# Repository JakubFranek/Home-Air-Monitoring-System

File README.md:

# Home Air Monitoring System

**Home Air Monitoring System (HAMS)** is my personal hardware & embedded software development project designed to monitor indoor and outdoor air quality in my home.

## Overview

The system consists of a [**central hub**](./docs/hub.md) and [**six wireless sensor nodes**](./docs/node.md) to measure:

- Temperature
- Relative Humidity
- Atmospheric Pressure
- Particulate Matter
- Volatile Organic Compounds (VOCs)
- NOₓ
- CO₂

## System Components

- **Central Hub**
   - **ESP32-based**; mains-powered.
   - Connects to the internet for weather updates and time synchronization via SNTP.
   - Displays real-time measurements on a 7.5" 800x480 e-ink screen with a 1 minute refresh rate.
   - Contains sensors for all previously listed quantities.
   - Screen-sized 3D-printed enclosure (estimated 175 mm x 92.65 mm x 120 mm).

- **Sensor Nodes**
   - **STM32-based** and battery-powered, optimized for low power consumption and long battery life.
   - Equipped with temperature and humidity sensors only, with optional hardware support for one more sensor.
   - Transmit data to the hub every minute using nRF24 radio modules.
   - Minimalistic and visually non-intrusive 3D-printed case with a small form factor (estimated 81 mm x 58 mm x 28 mm).

## Sensors

- **SHT40**
   - Temperature and humidity sensor from Sensirion.
   - Used in the central hub and sensor nodes.
   - Temperature accuracy: ±0.2 °C
   - Humidity accuracy: ±1.8 %RH
- **SCD41**
   - CO2 sensor from Sensirion.
   - Used in the central hub.
   - CO2 accuracy: ±50 ppm ± 5.0 %m.v. (depending on range)
- **SGP41**
   - VOC and NOx gas index sensor from Sensirion.
   - Used in the central hub.
- **SPS30**
   - Particulate matter sensor from Sensirion.
   - Used in the central hub.
   - Accuracy: ±10 %
- **BME280**
   - Temperature, relative humidity and atmospheric pressure sensor from Adafruit.
   - Used in the central hub (for atmospheric pressure only).
   - Atmospheric pressure accuracy: ±1 hPa

## Documentation

- [Hub](./docs/hub.md)
- [Nodes](./docs/node.md)
- [SHT4x calibration](./docs/sht4x_calibration.md)

## Repository Structure

```plaintext
├── docs                         # Documentation for project setup, usage, etc.
├── utilities                    # Various auxiliary scripts, tools etc.
│   ├── sht_sensor_burn_in       # PlatformIO Arduino project for SHT40 sensor burn-in
│   └── sht_sensor_calibration   # PlatformIO Arduino project for SHT40 sensor calibration
├── hub
│   ├── hardware                 # PCB design and schematic for hub
│   ├── firmware                 # Firmware for the ESP32-based central hub
│   └── 3D_models                # 3D models for the hub's enclosure
├── node
│   ├── firmware                 # Firmware for the STM32-based sensor nodes
│   ├── hardware                 # PCB designs and schematics for nodes
│   └── 3D_models                # 3D models for the nodes' enclosures
├── README.md                    # Project overview (you are reading this now!)
└── TODO.md                      # Project task list

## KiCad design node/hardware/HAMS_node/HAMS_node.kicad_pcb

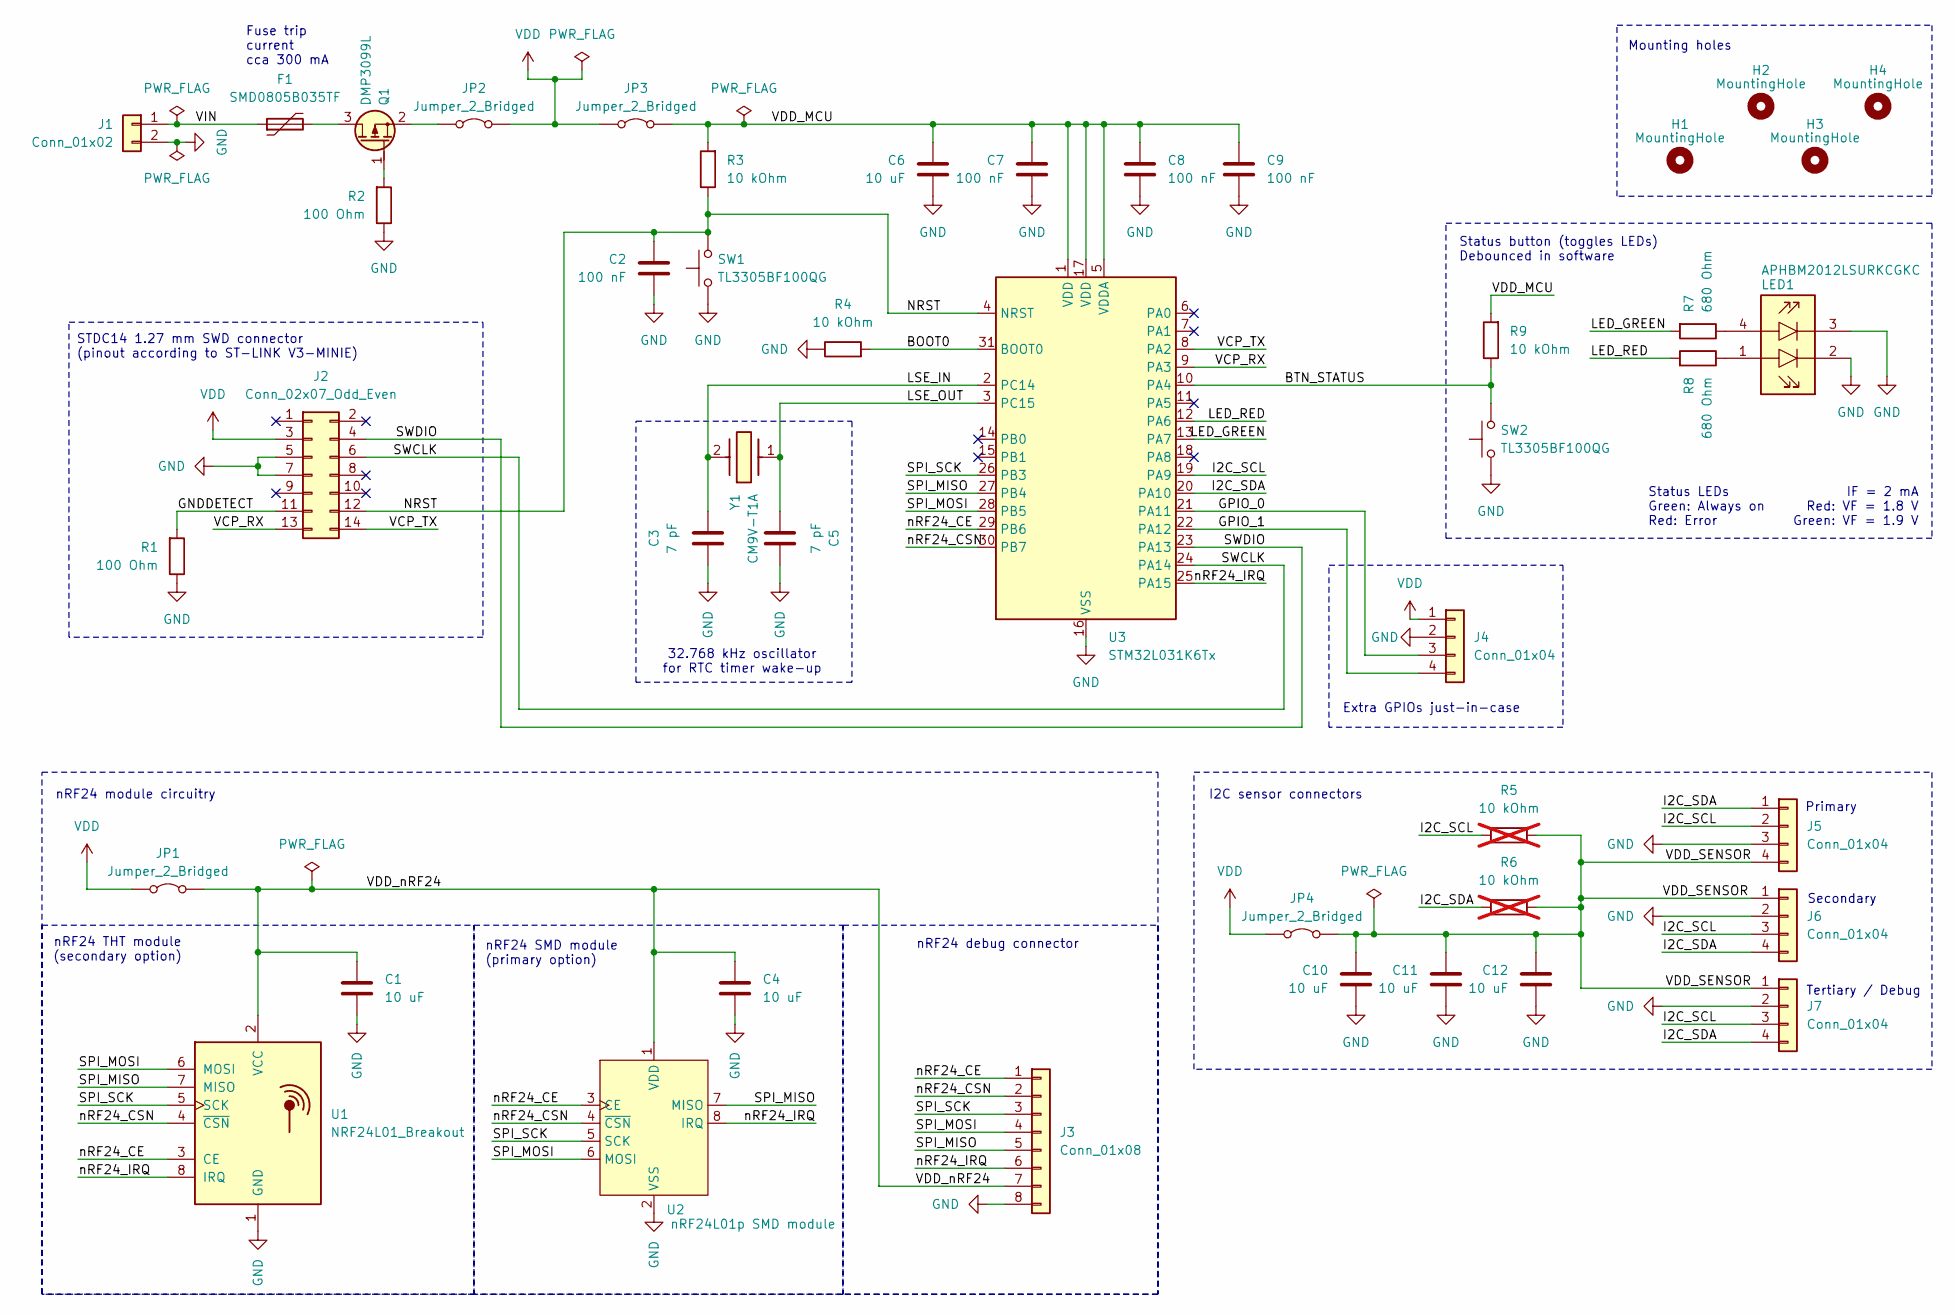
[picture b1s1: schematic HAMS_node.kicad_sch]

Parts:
C1, C4, C6, C10, C11, C12: 10 uF; C_0603_1608Metric_Pad1.08x0.95mm_HandSolder
C2, C7, C8, C9: 100 nF; C_0603_1608Metric_Pad1.08x0.95mm_HandSolder
C3, C5: 7 pF; C_0603_1608Metric_Pad1.08x0.95mm_HandSolder
F1: SMD0805B035TF; YAGEO_SMD0805_Fuse
H1, H2, H3, H4: MountingHole; MountingHole_2.2mm_M2_ISO7380
J1: Conn_01x02; JST_XH_B2B-XH-AM_1x02_P2.50mm_Vertical
J2: Conn_02x07_Odd_Even; PinHeader_2x07_P1.27mm_Vertical_SMD
J3: Conn_01x08; PinSocket_1x08_P2.54mm_Vertical
J4, J7: Conn_01x04; PinSocket_1x04_P2.54mm_Vertical
J5, J6: Conn_01x04; PinSocket_1x04_P2.54mm_Horizontal
JP1, JP2, JP3, JP4: Jumper_2_Bridged; PinHeader_1x02_P1.27mm_Vertical
LED1: APHBM2012LSURKCGKC; KPHBM2012QBDCGKC; Mouser Part Number 604-APHBM2012LSURKCG
Q1: DMP3099L; SOT-23
R1, R2: 100 Ohm; R_0603_1608Metric_Pad0.98x0.95mm_HandSolder
R3, R4, R9: 10 kOhm; R_0603_1608Metric_Pad0.98x0.95mm_HandSolder
R5, R6: 10 kOhm; R_0603_1608Metric_Pad0.98x0.95mm_HandSolder; not fitted
R7, R8: 680 Ohm; R_0603_1608Metric_Pad0.98x0.95mm_HandSolder
SW1, SW2: TL3305BF100QG; E-Switch_TL3305BF100QG_Tactile_SPST
U1: NRF24L01_Breakout; nRF24L01_Breakout
U2: nRF24L01p SMD module; nRF24L01p_SMD_module
U3: STM32L031K6Tx; LQFP-32_7x7mm_P0.8mm
Y1: CM9V-T1A; Crystal_SMD_MicroCrystal_CM9V-T1A-2Pin_1.6x1.0mm_BigPads; Mouser Part Number 428-202416-MC01

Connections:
/BOOT0: R4.2, U3.31 (BOOT0)
/BTN_STATUS: R9.1, SW2.2, U3.10 (PA4)
/GNDDETECT: J2.11, R1.2
/GPIO_0: J4.3, U3.21 (PA11)
/GPIO_1: J4.4, U3.22 (PA12)
/I2C_SCL: J5.2, J6.3, J7.3, R5.1, U3.19 (PA9)
/I2C_SDA: J5.1, J6.4, J7.4, R6.1, U3.20 (PA10)
/LED_GREEN: R7.2, U3.13 (PA7)
/LED_RED: R8.2, U3.12 (PA6)
/LSE_IN: C3.1, U3.2 (PC14), Y1.2 (X2)
/LSE_OUT: C5.1, U3.3 (PC15), Y1.1 (X1)
/NRST: C2.1, J2.12, R3.1, SW1.2, U3.4 (NRST)
/SPI_MISO: J3.5, U1.7 (MISO), U2.7 (MISO), U3.27 (PB4)
/SPI_MOSI: J3.4, U1.6 (MOSI), U2.6 (MOSI), U3.28 (PB5)
/SPI_SCK: J3.3, U1.5 (SCK), U2.5 (SCK), U3.26 (PB3)
/SWCLK: J2.6, U3.24 (PA14)
/SWDIO: J2.4, U3.23 (PA13)
/VCP_RX: J2.13, U3.9 (PA3)
/VCP_TX: J2.14, U3.8 (PA2)
/VDD_MCU: C6.1, C7.1, C8.1, C9.1, JP3.2 (B), R3.2, R9.2, U3.1 (VDD), U3.5 (VDDA), U3.17 (VDD)
/VDD_SENSOR: C10.1, C11.1, C12.1, J5.4, J6.1, J7.1, JP4.2 (B), R5.2, R6.2
/VDD_nRF24: C1.2, C4.2, J3.7, JP1.2 (B), U1.2 (VCC), U2.1 (VDD)
/VIN: F1.1, J1.1
/nRF24_CE: J3.1, U1.3 (CE), U2.3 (CE), U3.29 (PB6)
/nRF24_CSN: J3.2, U1.4 (~CSN), U2.4 (~CSN), U3.30 (PB7)
/nRF24_IRQ: J3.6, U1.8 (IRQ), U2.8 (IRQ), U3.25 (PA15)
GND: C1.1, C2.2, C3.2, C4.1, C5.2, C6.2, C7.2, C8.2, C9.2, C10.2, C11.2, C12.2, J1.2, J2.5, J2.7, J3.8, J4.2, J5.3, J6.2, J7.2, LED1.2 (CATHODE_RED), LED1.3 (CATHODE_GREEN), R1.1, R2.1, R4.1, SW1.1, SW2.1, U1.1 (GND), U2.2 (VSS), U3.16 (VSS), U3.32 (VSS)
unnamed: JP2.1 (A), Q1.2 (S)
unnamed: LED1.4 (ANODE_GREEN), R7.1
unnamed: LED1.1 (ANODE_RED), R8.1
unnamed: F1.2, Q1.3 (D)
unnamed: Q1.1 (G), R2.2
VDD: J2.3, J4.1, JP1.1 (A), JP2.2 (B), JP3.1 (A), JP4.1 (A)

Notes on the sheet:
nRF24 THT module (secondary option)
IF = 2 mA Red: VF = 1.8 V Green: VF = 1.9 V
nRF24 SMD module (primary option)
32.768 kHz oscillator for RTC timer wake-up
Mounting holes
Fuse trip current cca 300 mA
Status LEDs Green: Always on Red: Error
Secondary
nRF24 debug connector
Tertiary / Debug
Status button (toggles LEDs) Debounced in software
STDC14 1.27 mm SWD connector (pinout according to ST-LINK V3-MINIE)
Primary
Extra GPIOs just-in-case
I2C sensor connectors
nRF24 module circuitry

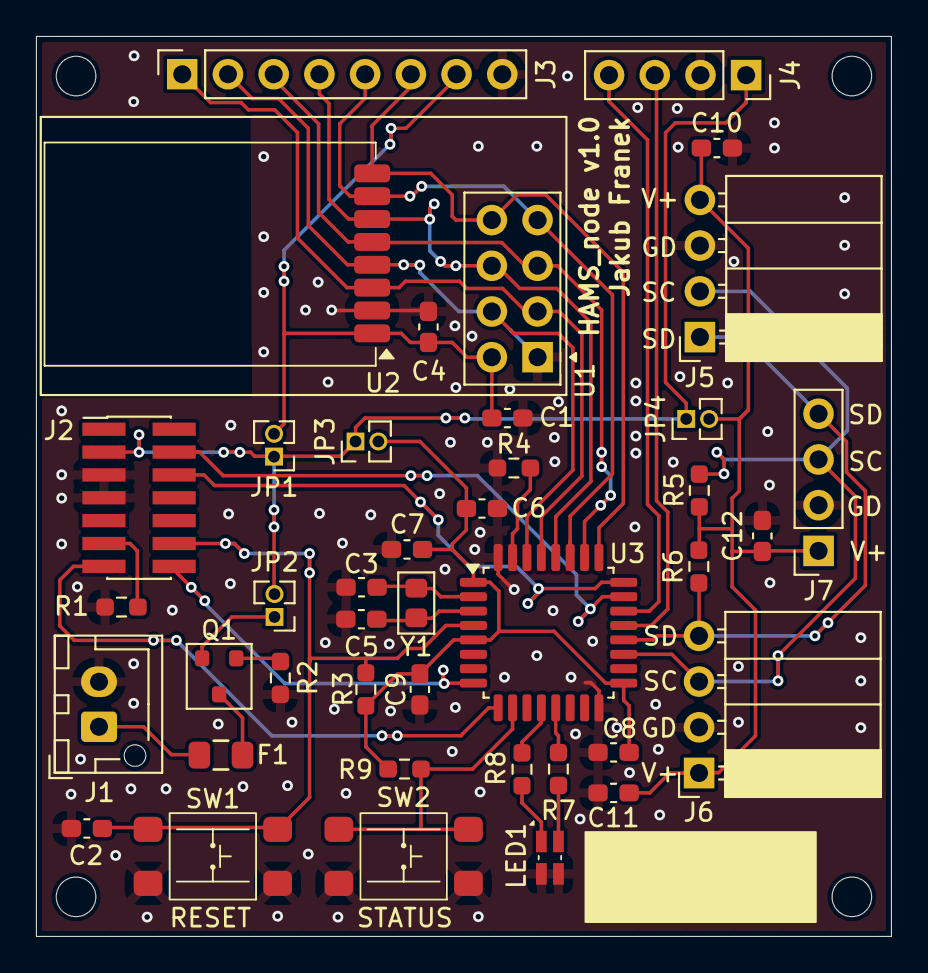
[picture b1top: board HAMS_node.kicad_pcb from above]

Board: 2 copper layers, 47.5 x 50.0 mm, 45 parts (0 on the bottom side), 33 nets.

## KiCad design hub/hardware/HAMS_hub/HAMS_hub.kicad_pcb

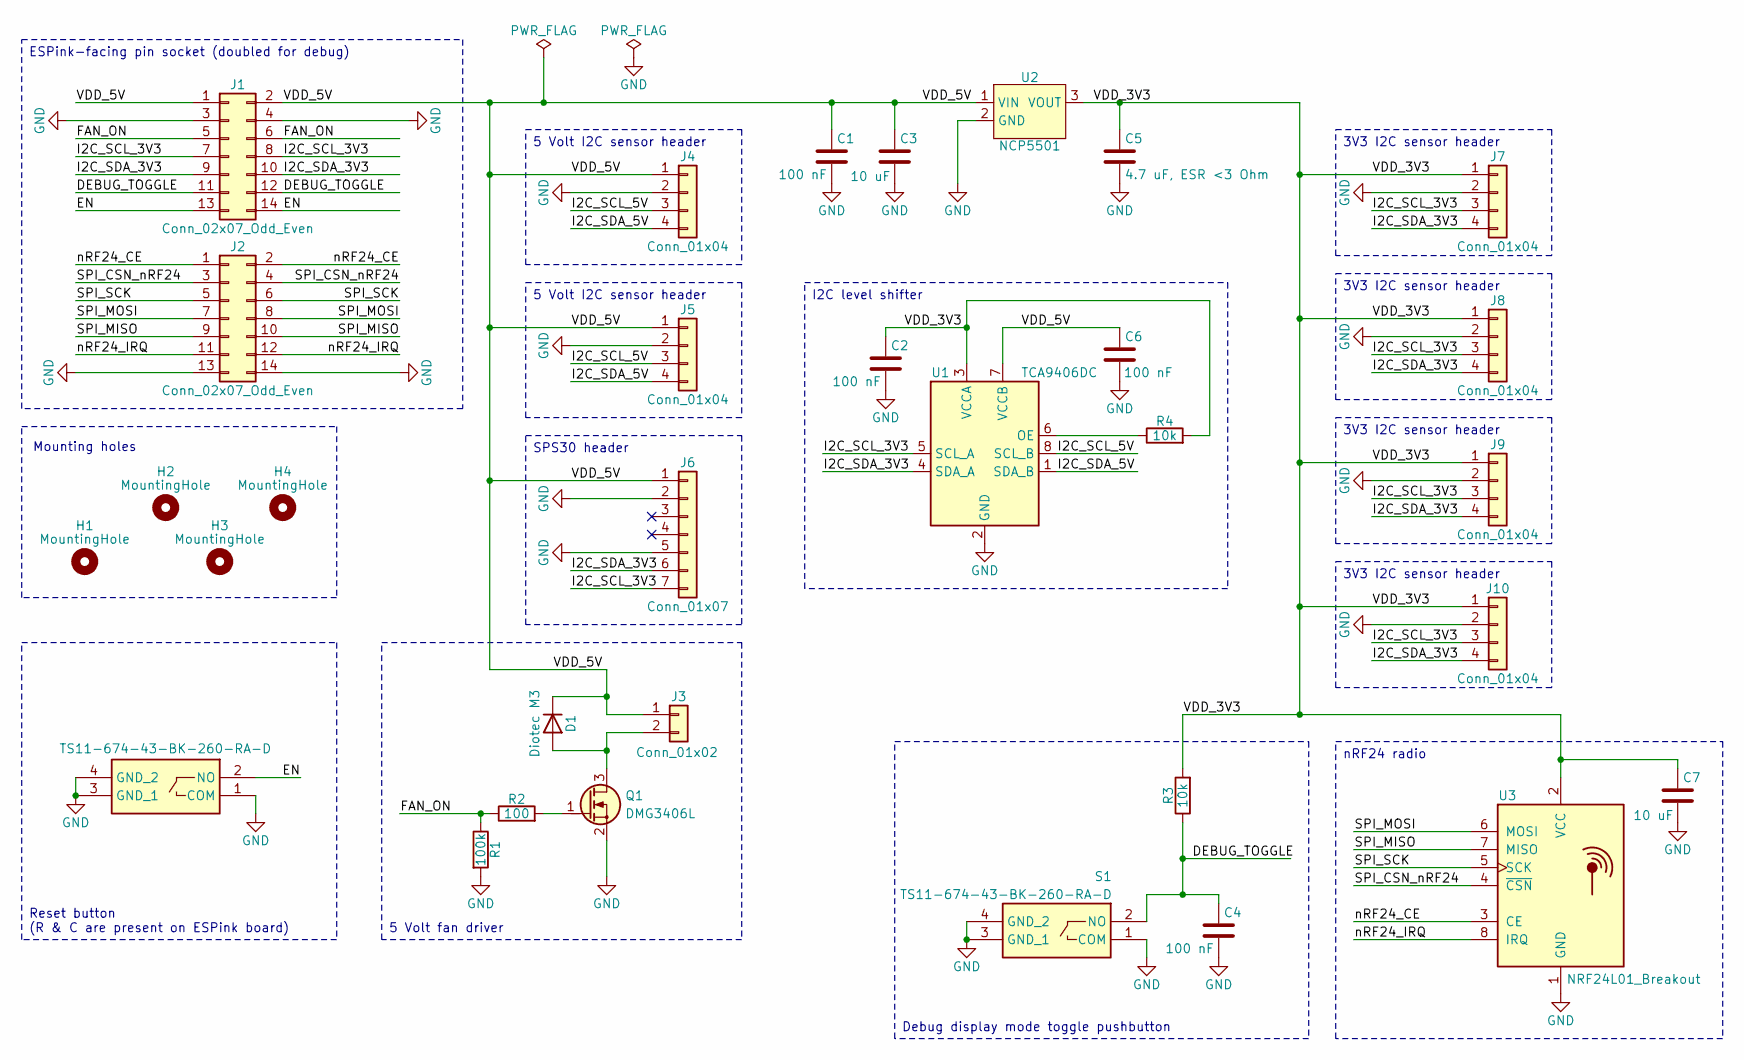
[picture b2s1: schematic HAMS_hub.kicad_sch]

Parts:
C1, C2, C4, C6: 100 nF; C_0805_2012Metric_Pad1.18x1.45mm_HandSolder
C3, C7: 10 uF; C_0805_2012Metric_Pad1.18x1.45mm_HandSolder
C5: 4.7 uF, ESR <3 Ohm; C_0805_2012Metric_Pad1.18x1.45mm_HandSolder
D1: Diotec M3; D_SMA_Handsoldering
H1, H2, H3, H4: MountingHole; MountingHole_2.2mm_M2_ISO7380
J1, J2: Conn_02x07_Odd_Even; PinSocket_2x07_P2.54mm_Vertical
J3: Conn_01x02; PinHeader_1x02_P2.54mm_Vertical
J4, J5, J7, J8, J9, J10: Conn_01x04; PinSocket_1x04_P2.54mm_Vertical
J6: Conn_01x07; PinHeader_1x07_P2.54mm_Vertical
Q1: DMG3406L; SOT-23
R1: 100k; R_0805_2012Metric_Pad1.20x1.40mm_HandSolder
R2: 100; R_0805_2012Metric_Pad1.20x1.40mm_HandSolder
R3, R4: 10k; R_0805_2012Metric_Pad1.20x1.40mm_HandSolder
S1, S2: TS11-674-43-BK-260-RA-D; TS1167443BK260RAD; Mouser Part Number 179-TS1167443260RAD
U1: TCA9406DC; SSOP-8_2.95x2.8mm_P0.65mm
U2: NCP5501; TO-252-2
U3: NRF24L01_Breakout; nRF24L01_Breakout

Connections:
/DEBUG_TOGGLE: C4.1, J1.11, J1.12, R3.1, S1.2 (NO)
/EN: J1.13, J1.14, S2.2 (NO)
/FAN_ON: J1.5, J1.6, R1.1, R2.1
/I2C_SCL_3V3: J1.7, J1.8, J6.7, J7.3, J8.3, J9.3, J10.3, U1.5 (SCL_A)
/I2C_SCL_5V: J4.3, J5.3, U1.8 (SCL_B)
/I2C_SDA_3V3: J1.9, J1.10, J6.6, J7.4, J8.4, J9.4, J10.4, U1.4 (SDA_A)
/I2C_SDA_5V: J4.4, J5.4, U1.1 (SDA_B)
/SPI_CSN_nRF24: J2.3, J2.4, U3.4 (~CSN)
/SPI_MISO: J2.9, J2.10, U3.7 (MISO)
/SPI_MOSI: J2.7, J2.8, U3.6 (MOSI)
/SPI_SCK: J2.5, J2.6, U3.5 (SCK)
/VDD_3V3: C2.1, C5.1, C7.1, J7.1, J8.1, J9.1, J10.1, R3.2, R4.2, U1.3 (VCCA), U2.3 (VOUT), U3.2 (VCC)
/VDD_5V: C1.1, C3.1, C6.1, D1.1 (K), J1.1, J1.2, J3.1, J4.1, J5.1, J6.1, U1.7 (VCCB), U2.1 (VIN)
/nRF24_CE: J2.1, J2.2, U3.3 (CE)
/nRF24_IRQ: J2.11, J2.12, U3.8 (IRQ)
GND: C1.2, C2.2, C3.2, C4.2, C5.2, C6.2, C7.2, J1.3, J1.4, J2.13, J2.14, J4.2, J5.2, J6.2, J6.5, J7.2, J8.2, J9.2, J10.2, Q1.2 (S), R1.2, S1.1 (COM), S1.3 (GND_1), S1.4 (GND_2), S2.1 (COM), S2.3 (GND_1), S2.4 (GND_2), U1.2 (GND), U2.2 (GND), U3.1 (GND)
unnamed: D1.2 (A), J3.2, Q1.3 (D)
unnamed: Q1.1 (G), R2.2
unnamed: R4.1, U1.6 (OE)

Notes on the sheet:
Mounting holes
Debug display mode toggle pushbutton
3V3 I2C sensor header
5 Volt I2C sensor header
5 Volt fan driver
ESPink-facing pin socket (doubled for debug)
nRF24 radio
I2C level shifter
SPS30 header
Reset button (R & C are present on ESPink board)

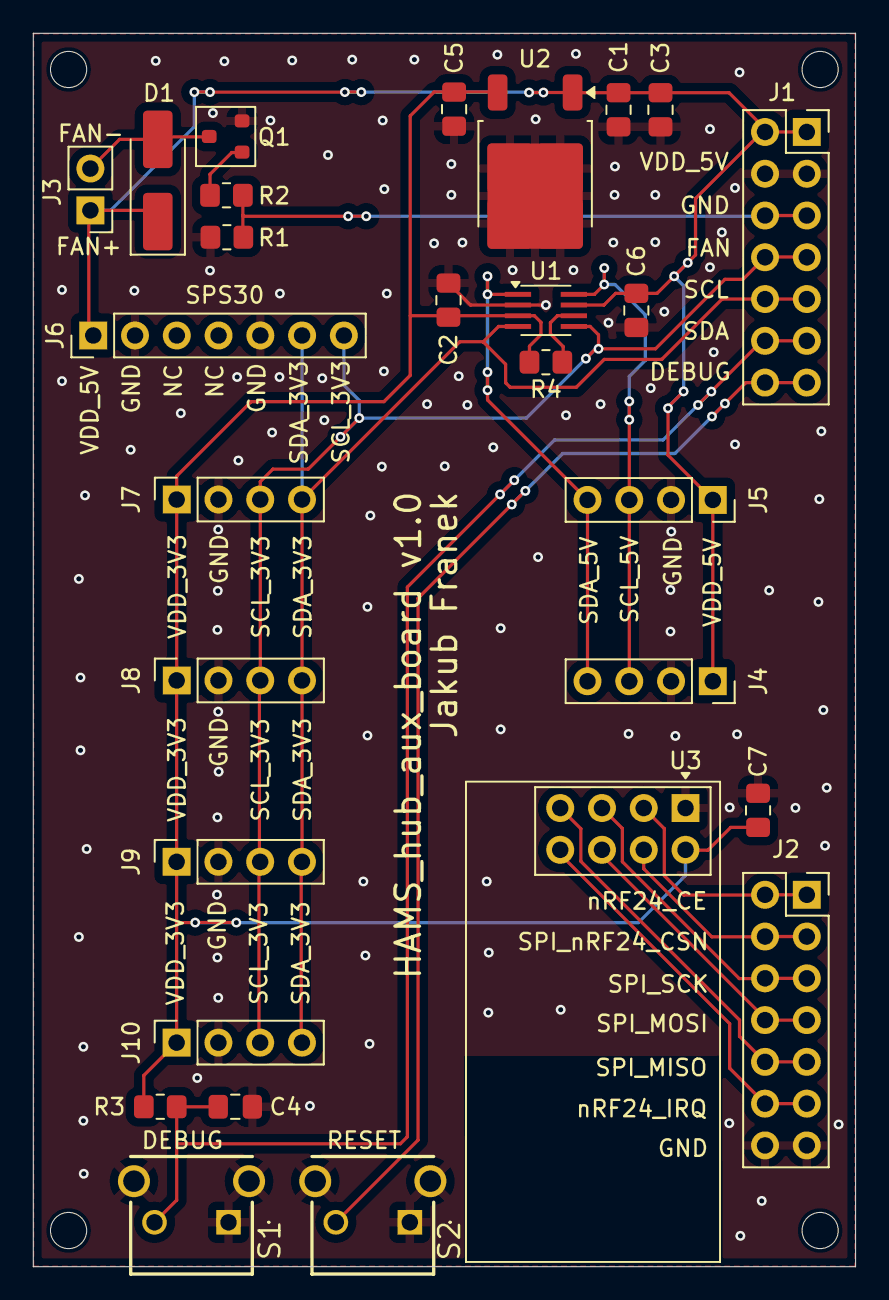
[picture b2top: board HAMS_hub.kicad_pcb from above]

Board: 2 copper layers, 50.0 x 75.0 mm, 32 parts (0 on the bottom side), 19 nets.

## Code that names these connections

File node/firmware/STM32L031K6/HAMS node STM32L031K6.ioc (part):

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Mcu.Name=STM32L031K(4-6)Tx
Mcu.Package=LQFP32
Mcu.UserName=STM32L031K6Tx
PA10.GPIOParameters=GPIO_Speed,GPIO_Label
PA10.GPIO_Label=I2C_SDA
PA10.GPIO_Speed=GPIO_SPEED_FREQ_LOW
PA10.Mode=I2C
PA10.Signal=I2C1_SDA
PA13.Mode=Serial_Wire
PA13.Signal=SYS_SWDIO
PA14.Mode=Serial_Wire
PA14.Signal=SYS_SWCLK
PA15.GPIOParameters=GPIO_Label,GPIO_ModeDefaultEXTI
PA15.GPIO_Label=nRF24_IRQ
PA15.GPIO_ModeDefaultEXTI=GPIO_MODE_IT_FALLING
PA15.Signal=GPXTI15
PA2.Mode=Asynchronous
PA2.Signal=USART2_TX
PA3.Mode=Asynchronous
PA3.Signal=USART2_RX
PA4.GPIOParameters=GPIO_Label,GPIO_ModeDefaultEXTI
PA4.GPIO_Label=BUTTON_LED
PA4.GPIO_ModeDefaultEXTI=GPIO_MODE_IT_FALLING
PA4.Signal=GPXTI4
PA6.GPIOParameters=GPIO_Label
PA6.GPIO_Label=LED_ERROR
PA6.Signal=GPIO_Output
PA7.GPIOParameters=GPIO_Label
PA7.GPIO_Label=LED_STATUS
PA7.Signal=GPIO_Output
PA9.GPIOParameters=GPIO_Speed,GPIO_Label
PA9.GPIO_Label=I2C_SCL
PA9.GPIO_Speed=GPIO_SPEED_FREQ_LOW
PA9.Mode=I2C
PA9.Signal=I2C1_SCL
PB3.GPIOParameters=GPIO_Label
PB3.GPIO_Label=SPI_SCK
PB3.Mode=Full_Duplex_Master
PB3.Signal=SPI1_SCK
PB4.GPIOParameters=GPIO_Label
PB4.GPIO_Label=SPI_MISO
PB4.Mode=Full_Duplex_Master
PB4.Signal=SPI1_MISO
PB5.GPIOParameters=GPIO_Label
PB5.GPIO_Label=SPI_MOSI
PB5.Mode=Full_Duplex_Master
PB5.Signal=SPI1_MOSI
PB6.GPIOParameters=GPIO_Label
PB6.GPIO_Label=nRF24_CE
PB6.Signal=GPIO_Output
PB7.GPIOParameters=GPIO_Label
PB7.GPIO_Label=nRF24_CSN
PB7.Signal=GPIO_Output
PC14-OSC32_IN.GPIOParameters=GPIO_Label
PC14-OSC32_IN.GPIO_Label=LSE_IN
PC14-OSC32_IN.Mode=LSE-External-Oscillator
PC14-OSC32_IN.Signal=RCC_OSC32_IN
PC15-OSC32_OUT.GPIOParameters=GPIO_Label
PC15-OSC32_OUT.GPIO_Label=LSE_OUT
PC15-OSC32_OUT.Mode=LSE-External-Oscillator
PC15-OSC32_OUT.Signal=RCC_OSC32_OUT
RCC.HSE_VALUE=8000000
RCC.SYSCLKFreq_VALUE=8000000
RCC.SYSCLKSource=RCC_SYSCLKSOURCE_PLLCLK
board=custom

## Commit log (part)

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2024-11-07 Initial commit
    Transmitter code in incomplete state.
    Initial README.md implementation.
2024-11-07 Improve HAMS node FW: stop mode, bug fixes
    Improve stop mode current consumption (<1 uA reached).
    Add several pin user labels.
    Set unused pins to analog mode.
    Fix bug: incorrect I2C/SPI timeout logic.
    Fix bug: event flags cleared incorrectly in app.c.
2024-11-08 Improve HAMS node FW: refactoring, bug fixes
    Add macros to make app.c code less repetitive.
    Disable LED pin (not used in final application).
    Fix bug: large stop mode current consumption (pins not set to analog
    mode).
2024-11-09 Improve HAMS node FW: f_CLK, sleep, SPI
    Lower clock from 32 MHz to 8 MHz.
    Increase I2C and SPI frequency 4x.
    Enter sleep mode when waiting for timer and nRF24 interrupts.
    Force nRF24_CE pin low during stop mode.
    Add SPI1_Transmit_Multi function optimized for transmitting multiple
    bytes in quick succession.
2024-11-09 Improve HAMS node FW: optimize SPI, refactor
    Optimize SPI custom functions for speed.
    Make all SPI and I2C custom functions handle multi-byte transfers.
    Add const modifiers to relevant function signatures.
    Remove redundant status code returns from many functions.
2024-11-09 Improve HAMS node FW: ADC, app errors, refactoring
    Measure VDDA via ADC and send it via nRF24 in payload.
    Add more AppError enum members, modify error checking macros in app.c to
    use them.
2024-12-02 Improve HAMS node FW: fix bug, format, add TODO
2024-12-02 Update task list
2024-12-17 Update task list, add resource images
2024-12-18 Add initial HAMS hub FW
    Initial commit of HAMS hub firmware (copied from EPD demo project).
    Update .gitignore.
2024-12-18 Improve HAMS hub FW
    Move display functions to a separate file.
    Add custom memory partition table (code would not fit in default
    1 MB partition).
    Implement WiFi station module.
    Implement SNTP module.
    Implement svatkyAPI.cz module.
2024-12-19 Improve HAMS hub FW: SHT4x & SGP41 sensors
    Add sensor_control module with support for SHT4x and SGP41 sensors.
    Add timeout to openweathermap_api request_weather_data function.
    Add timeout to svatky_api request_svatky_data function.
    Rename wifi_sta to wifi_station.
2024-12-19 Improve HAMS hub FW: BME280 sensor
    Add support for BME280 sensor.
2024-12-19 Improve HAMS hub FW: SCD41 sensor
    Add support for SCD41 sensor.
    Add Sgp41Device.sampling_period_s member.
2024-12-19 Improve HAMS hub FW: SPS30 sensor
    Add support for SPS30 sensor.
    Add delay function pointer to SGP41 driver to fix I2C errors.
    Merge sgp41_execute_self_test and sgp41_evaluate_self_test into one
    function.
2024-12-19 Improve HAMS hub FW: SPS30 sensor
    Increase I2C function timeout periods to 20 ms.
    Add code to main.cpp to print formatted timezone-aware time.
2024-12-19 Improve HAMS node FW: fix bug, lengthen sleep
    Lengthen sleep to 10 seconds.
    Fix bug: received data is 3 transmissions delayed (flush nRF24 TX FIFO
    before transmitting).
2024-12-19 Improve HAMS hub FW: refactor
    Add how-to guides to BME280 and nRF24 drivers.
    Move private nRF24 driver defines from .h to .c file.
2024-12-20 Improve HAMS node FW: refactor, fix bug
    Rename app_error variable to app_status.
    Add another TX FIFO flush command to prevent delayed data transmissions.
    Update task list.
2024-12-20 Improve HAMS hub FW: add timestamps
    Add timestamps to SvatkyApiData and WeatherData.
2024-12-20 Improve HAMS hub FW: refactor radio control
    Add nodes.h with node name and address definitions.
    Add timestamp to NodeData.
    Move NodeDataSet mutex to static radio_control.c variable.
2024-12-20 Improve HAMS hub FW: refactor radio control
    Remove NodeDataSet struct (it was only encapsulating a single array).
2024-12-20 Improve HAMS hub FW: fix bug, display real data
    Fix bug: radio_control function get_node_data does not copy data
    properly.
    Store hub's sensor data in SensorHubData struct.
    Show real data on e-ink display.
2024-12-20 Improve HAMS hub FW: startup sequence logging
    Add startup sequence logging to e-ink display to main.cpp.
    Update task list.
    Change FreeSans10pt7b yAdvance from 33 to 22 px.
    Add wifi_station docstrings, function status codes and function
    is_wifi_connected.
    Add sntp_api docstrings and function status codes.
2024-12-20 Improve HAMS hub FW: add debug mode
    Add button driven debug mode.
    Change get_wifi_ap_record to provide more information to DisplayData
    struct directly.
    Add svatkyapi and openweathermap update counts their data structs.
    Add SNTP debug info to DisplayData, and support it in sntp_api.
    Add measurement counts to SensorHubData struct.
2024-12-20 Improve HAMS hub FW: minor improvements
    Update task list.
    Use current date in svatkyapi request.
    Request new weather forecast as soon as the date changes.
    Add display_control function docstrings.
    Fix bug: replace Czech characters in the nameday name.
2024-12-21 Improve HAMS hub FW: minor improvements
    Add 8 pt font for debug mode.
    Improve debug mode layout and add app status code.
    Save sensor status codes to SensorHubData.
    Add synchronize_time function to sntp_api.
    Refactor sntp_api.
    Add connect_wifi method to wifi_station.
2024-12-21 Improve HAMS node FW: minor refactor
    Move flush command from phase 1 to phase 2 state.
    Fix flush command position in awaiting ack state
2024-12-21 Improve HAMS hub FW: improve debug mode
    Implement hub sensor error count debug mode values.
    Implement WiFi connection count debug mode value.
2024-12-21 Improve HAMS hub FW: handle invalid display data
    Display "--" when data is out of date or invalid.
2024-12-23 Improve HAMS hub FW: refactor, fix bugs
    Update task list.
    Add calendar_data, hams_data and weather_data headers which
    include common struct definitions.
    Create DebugData struct, which is now a member of HamsData
    (previously DisplayData).
    Fix bug: rain and snow WeatherData members not reset to zero when their
2024-12-27 Improve HAMS hub FW: refactor
    Add & improve comments/docstrings in multiple files.
    Rename nodes.h/c to node_constants.h/c.
    Rename sntp_api to sntp_control.
    Add get_sntp_stats function to sntp_api.
    Rename wifi_station to wifi_station_control.
    Add logging, connection counting, error checking to
2024-12-27 Improve HAMS hub FW: fix bug, utilize second CPU
    Fix bug: typical particulate matter particle size unit is nm, but
    should be um.
    Run task_nrf24_control on second core (PRO_CPU).
2024-12-28 Add calibration PlatformIO utility project
    Add utilities/temp_relhum_sensor_calibration PlatformIO project.
2024-12-28 Improve project docs and structure
    Update task list.
    Update README.
    Rename temp_relhum_sensor_calibration project to sht_sensor_calibration.
    Add tiny hub FW improvements.
2024-12-29 Add SHT40 burn-in PlatformIO utility project
    Update task list.
2024-12-30 Improve SHT40 calibration utility project
    Toggle MOSFET to draw more current periodically in order to prevent
    power bank from switching off.
2024-12-30 Improve HAMS node HW: add WIP PCB, edit schematic
    Update schematic significantly (adding nRF24 modules, specify parts, add
    notes etc).
    Add preliminary PCB layout (WIP).
2024-12-30 Improve HAMS node HW: PCB and device resize
    Change many 0805 devices for 0603 devices.
    Add mounting holes.
    Make the board 4.5 x 5 cm size.
2025-01-04 Improve HAMS node HW: PCB resize, optimization
    Optimize MCU pinout with respect to PCB routing.
    Change PCB size to 47.5 mm x 50 mm.
2025-01-05 Update task list
    Remove redundant .gitignore files.
2025-01-08 Improve HAMS node HW: schematic and PCB
    Add UART support to the ST-LINK programmer header.
    Update task list.
2025-01-15 Improve HAMS node HW: PCB
    Update HAMS_node PCB layout (minor position changes).
    Update task list.
2025-01-15 Improve HAMS hub FW: fix bug
    Fix bug: error codes printed in debug messages are unrelated to the
    given sensors.
2025-01-15 Add HAMS hub HW KiCad files (WIP)
    HAMS hub schematic is work-in-progress.
2025-01-17 Improve HAMS hub HW: schematic and PCB
    Improve schematic (add debug headers and mounting holes).
    Add DRC-clean PCB design.
    Update task list.
2025-01-26 Improve HAMS node FW: button driven status LEDs
    Add code for handling a button which causes status LEDs to light up.
2025-01-26 Improve HAMS node FW: remap pins
2025-01-27 Improve HAMS hub HW: reset button
    Add reset button.
2025-01-27 Improve HAMS hub HW: status button rework
    Replace toggle switch with tactile switch for status button.
2025-01-27 Update task list
    Check in .ioc HAMS node FW file.
2025-01-30 Add HAMS node & hub PCB gerbers
2025-02-08 Add HAMS node & hub 3D models, update task list
    Update task list.
    Update .gitignore.
    Add HAMS hub and node PCB 3D models.
    Add HAMS hub case 3D model.
2025-02-12 Update README and task list
2025-02-26 Update KiCAD files to version 9
2025-02-26 Add interactive BOMs
2025-02-26 Improve HAMS node FW: update nRF24 driver (bugged)
    Update task list.
2025-02-26 Improve HAMS node FW: fix nRF24 bug
    Fix bugged nRF24 by adding missing IRQ mask values when initializing
    nRF24 struct.
    Make leds_on and button_pending variables boolean.
2025-02-27 Improve HAMS node FW: auto retransmit delay
    Make nRF24 auto retransmit delay tied to node ID, so that it is
    unique for each node.
2025-03-01 Improve HAMS node FW: fix bugs, refactor UART logs
    Update task list.
    Fix bug: incorrect auto retransmit delay calculation.
    Refactor UART debug logging and debug mode (previously leds_on).
2025-03-01 Improve HAMS node HW & FW
    Add HAMS node small case 3D printing files.
    Update SHT4x driver in HAMS node firmware.
    Add comments and docstrings to HAMS node firmware.
    Update task list.
2025-03-01 Add firmware documentation
    Update task list.
2025-03-02 Add SHT4x calibration documentation
2025-03-05 Update 3D printing files
2025-03-09 Add hardware photos, update task list
2025-03-16 Improve HAMS node FW: fix bug, set period to 60 s
    Fix bug: nRF24 clones require CE pulse much longer than 10 us to
    transmit.
    Increase wake up period to 60 seconds.
2025-03-16 Update documentation
2025-03-16 Update hub FW
    Update task list.
    Rotate display to match enclosure orientation.
    Make 24h temperature minimum display optional and disable it.
    Add SCD41 FRC correction factor value to debug mode display.
    Simplify node info in debug display.
    Add code to allow SPS30 measurements at different rates (currently still
2025-03-16 Improve HAMS node & hub FW, fix bugs
    Set node and hub nRF24 data rate to 250 kbps.
    Fix bug: incorrect register bit field position values in nRF24 driver
    header.
    Fix bug: incorrect atmospheric pressure units.
    Rename node "Detsky pok." to "Detsky pokoj".
    Shorten node debug mode text.
2025-03-16 Update task list and README
2025-03-16 Fix node documentation
2025-03-17 Add 3D printing files, update task list
2025-03-17 Remove redundant 3D printing files
2025-03-17 Add image, improve README
2025-03-17 Remove redundant 3D printing file
2025-03-17 Improve documentation
    Fix image link in Markdown.
2025-05-08 Add issues doc
2025-05-08 Improve HAMS node FW: bug fix, slow down TIM21
    Slow down TIM21 by a factor of 10 (from 1 us to 10 us period),
    to allow scheduling interrupts for later.
    Fix bug: app_status not assigned in handle_state_awaiting_ack function
    when nRF24 IRQ times out.
    Fix bug: nRF24 IRQ flags not cleared at the start of cycle.
2026-02-13 Fix certificate issue
    Replace fixed .pem certificates with official certificate bundle.
    Add doc explaning the problem and both solutions.
    Updated ESP-IDF from 5.3.1 to 5.3.4.
2026-02-25 Migrate to svatky.steelants.cz API
